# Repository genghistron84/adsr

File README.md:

# adsr
Minimal footprint ADSR based on René Schmitz's "Fastest Envelop in the West" circuit

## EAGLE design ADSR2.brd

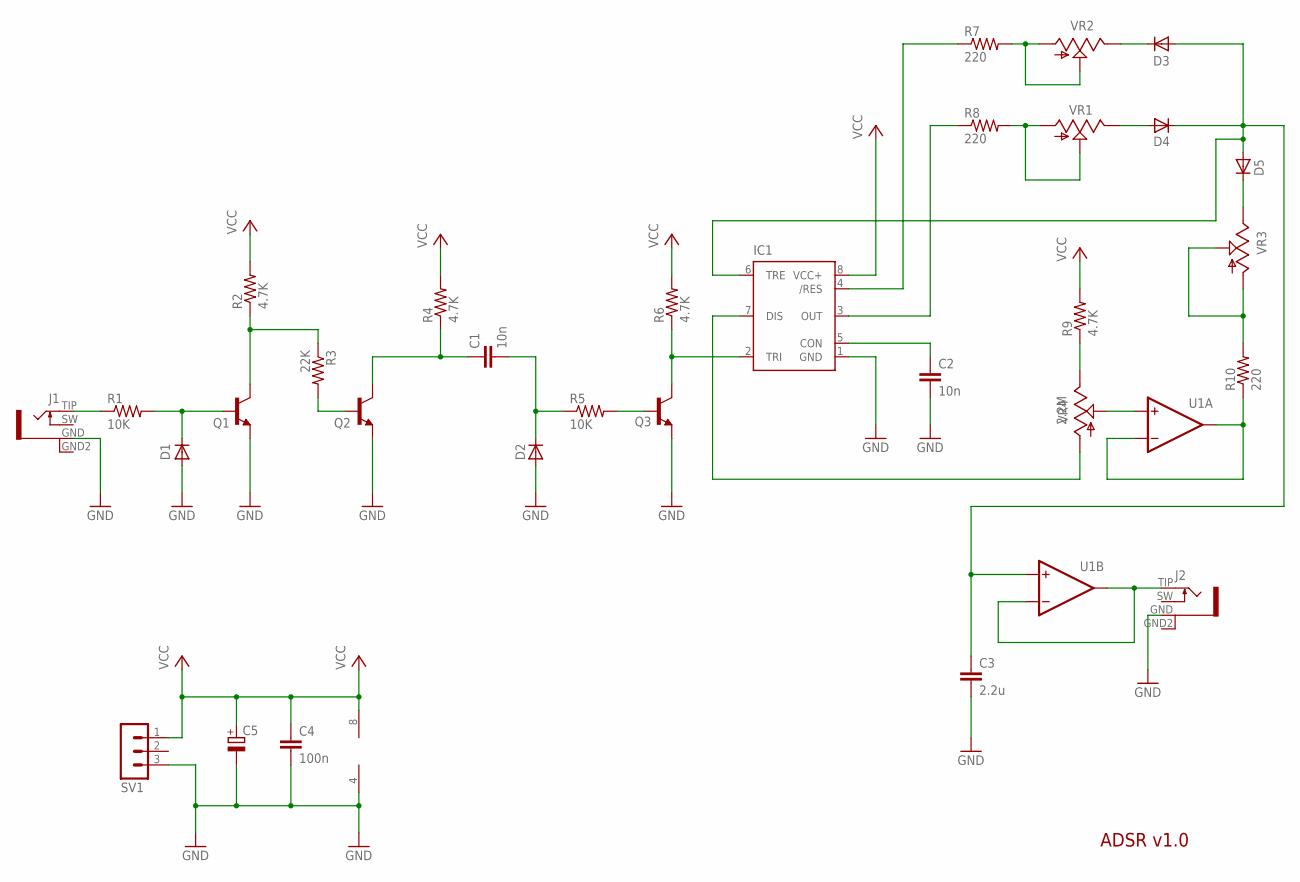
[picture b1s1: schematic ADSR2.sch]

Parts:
C1, C2: 10n; C025-025X050
C3: 2.2u; C025-025X050
C4: 100n; C025-025X050
C5: CPOL-EUE2,5-6E; E2,5-6E
D1, D2, D3, D4, D5: 1N4148DO35-7; DO35-7
IC1: 555; DIP08
J1, J2: PJ301WQP; THONK_JACK_P
Q1, Q2, Q3: 2N3904_TO92; TO92-EBC
R1, R5: 10K; 0207/10
R2, R4, R6, R9: 4.7K; 0207/10
R3: 22K; 0207/10
R7, R8, R10: 220; 0207/10
SV1: MA03-1
U1: TL072_DIL08; DIL08
VR1, VR2, VR3: 9MM_SNAP-IN_POT_; 9MM_SNAP-IN_POT
VR4: 2.2M; 9MM_SNAP-IN_POT

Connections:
GND: C2.2, C3.2, C4.2, C5.-, D1.A, D2.A, IC1.1 (GND), J1.GND (1), J2.GND (1), Q1.E, Q2.E, Q3.E, SV1.3, U1.4 (V-)
unnamed: J1.TIP (2), R1.1
unnamed: D1.C, Q1.B, R1.2
unnamed: Q2.B, R3.2
unnamed: Q3.B, R5.2
unnamed: C1.1, Q2.C, R4.1
unnamed: Q1.C, R2.1, R3.1
unnamed: C1.2, D2.C, R5.1
unnamed: IC1.2 (TRI), Q3.C, R6.1
unnamed: C2.1, IC1.5 (CON)
unnamed: R8.2, VR1.1 (A), VR1.2 (S)
unnamed: R7.2, VR2.1 (A), VR2.2 (S)
unnamed: D3.C, VR2.3 (E)
unnamed: D4.A, VR1.3 (E)
unnamed: IC1.3 (OUT), R8.1
unnamed: IC1.4 (/RES), R7.1
unnamed: J2.TIP (2), U1.6 (-IN), U1.7 (OUT)
unnamed: R10.2, VR3.1 (A), VR3.2 (S)
unnamed: D5.C, VR3.3 (E)
unnamed: IC1.7 (DIS), VR4.1 (A)
unnamed: C3.1, D3.A, D4.C, D5.A, IC1.6 (TRE), U1.5 (+IN)
unnamed: U1.3 (+IN), VR4.2 (S)
unnamed: R10.1, U1.1 (OUT), U1.2 (-IN)
unnamed: R9.1, VR4.3 (E)
VCC: C4.1, C5.+, IC1.8 (VCC+), R2.2, R4.2, R6.2, R9.2, SV1.1, U1.8 (V+)

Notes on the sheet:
ADSR v1.0

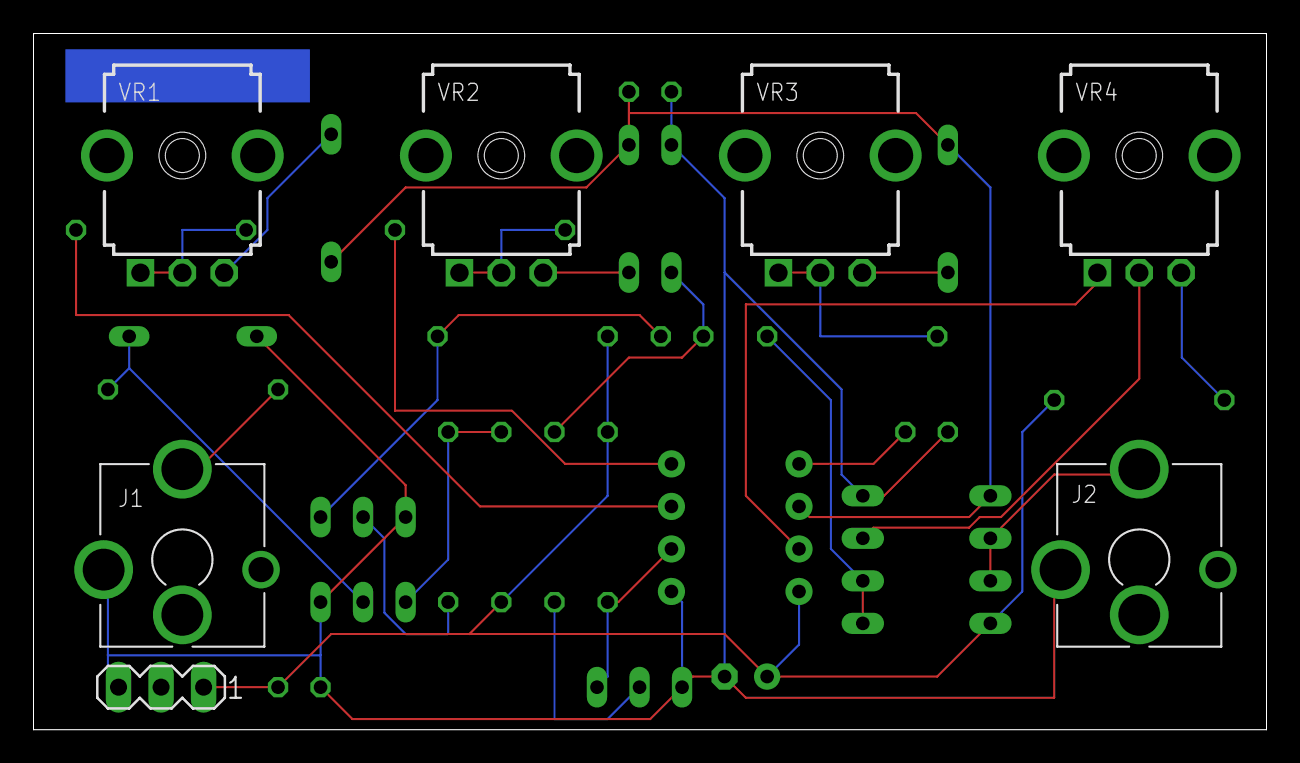
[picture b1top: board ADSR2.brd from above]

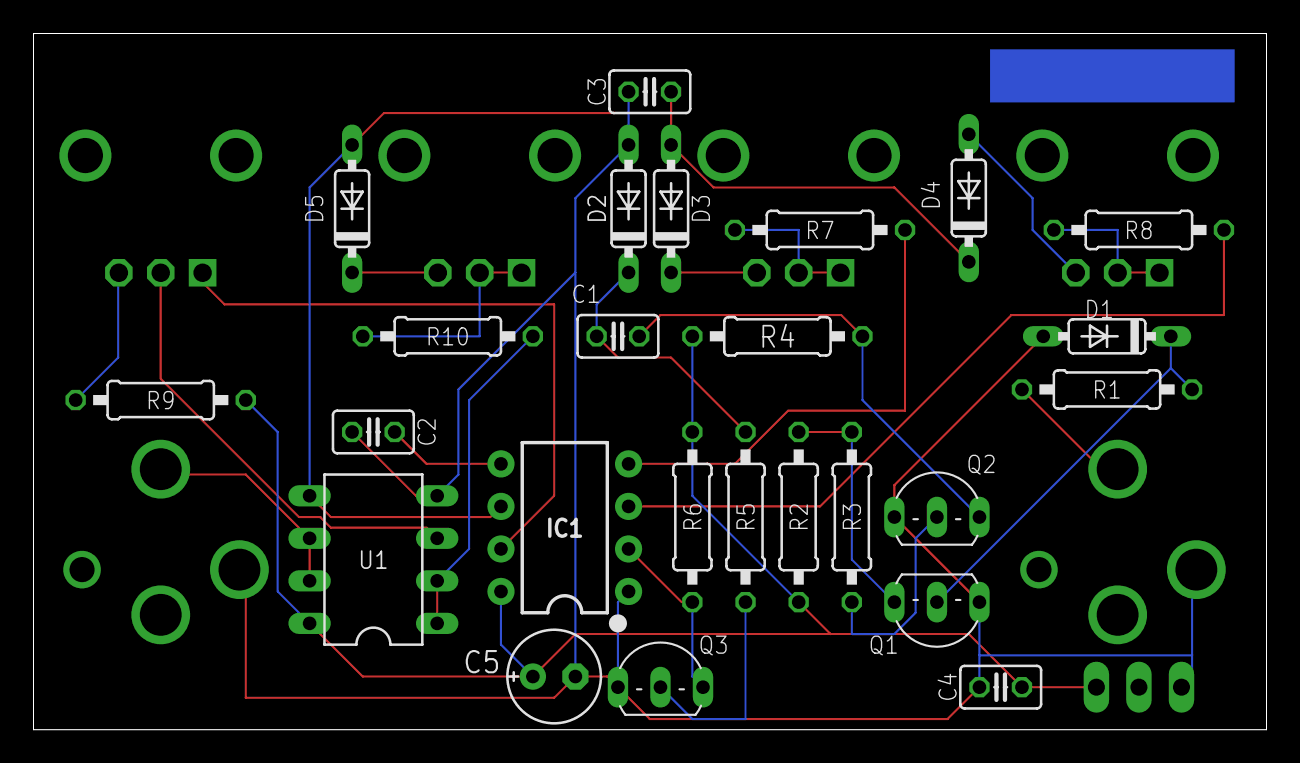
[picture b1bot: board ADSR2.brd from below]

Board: 2 copper layers, 73.6 x 41.6 mm, 32 parts (25 on the bottom side), 25 nets.

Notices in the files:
parts and their libraries:
SparkFun-IC-Special-Function: Licensing: Creative Commons ShareAlike 4.0 International - https://creativecommons.org/licenses/by-sa/4.0
